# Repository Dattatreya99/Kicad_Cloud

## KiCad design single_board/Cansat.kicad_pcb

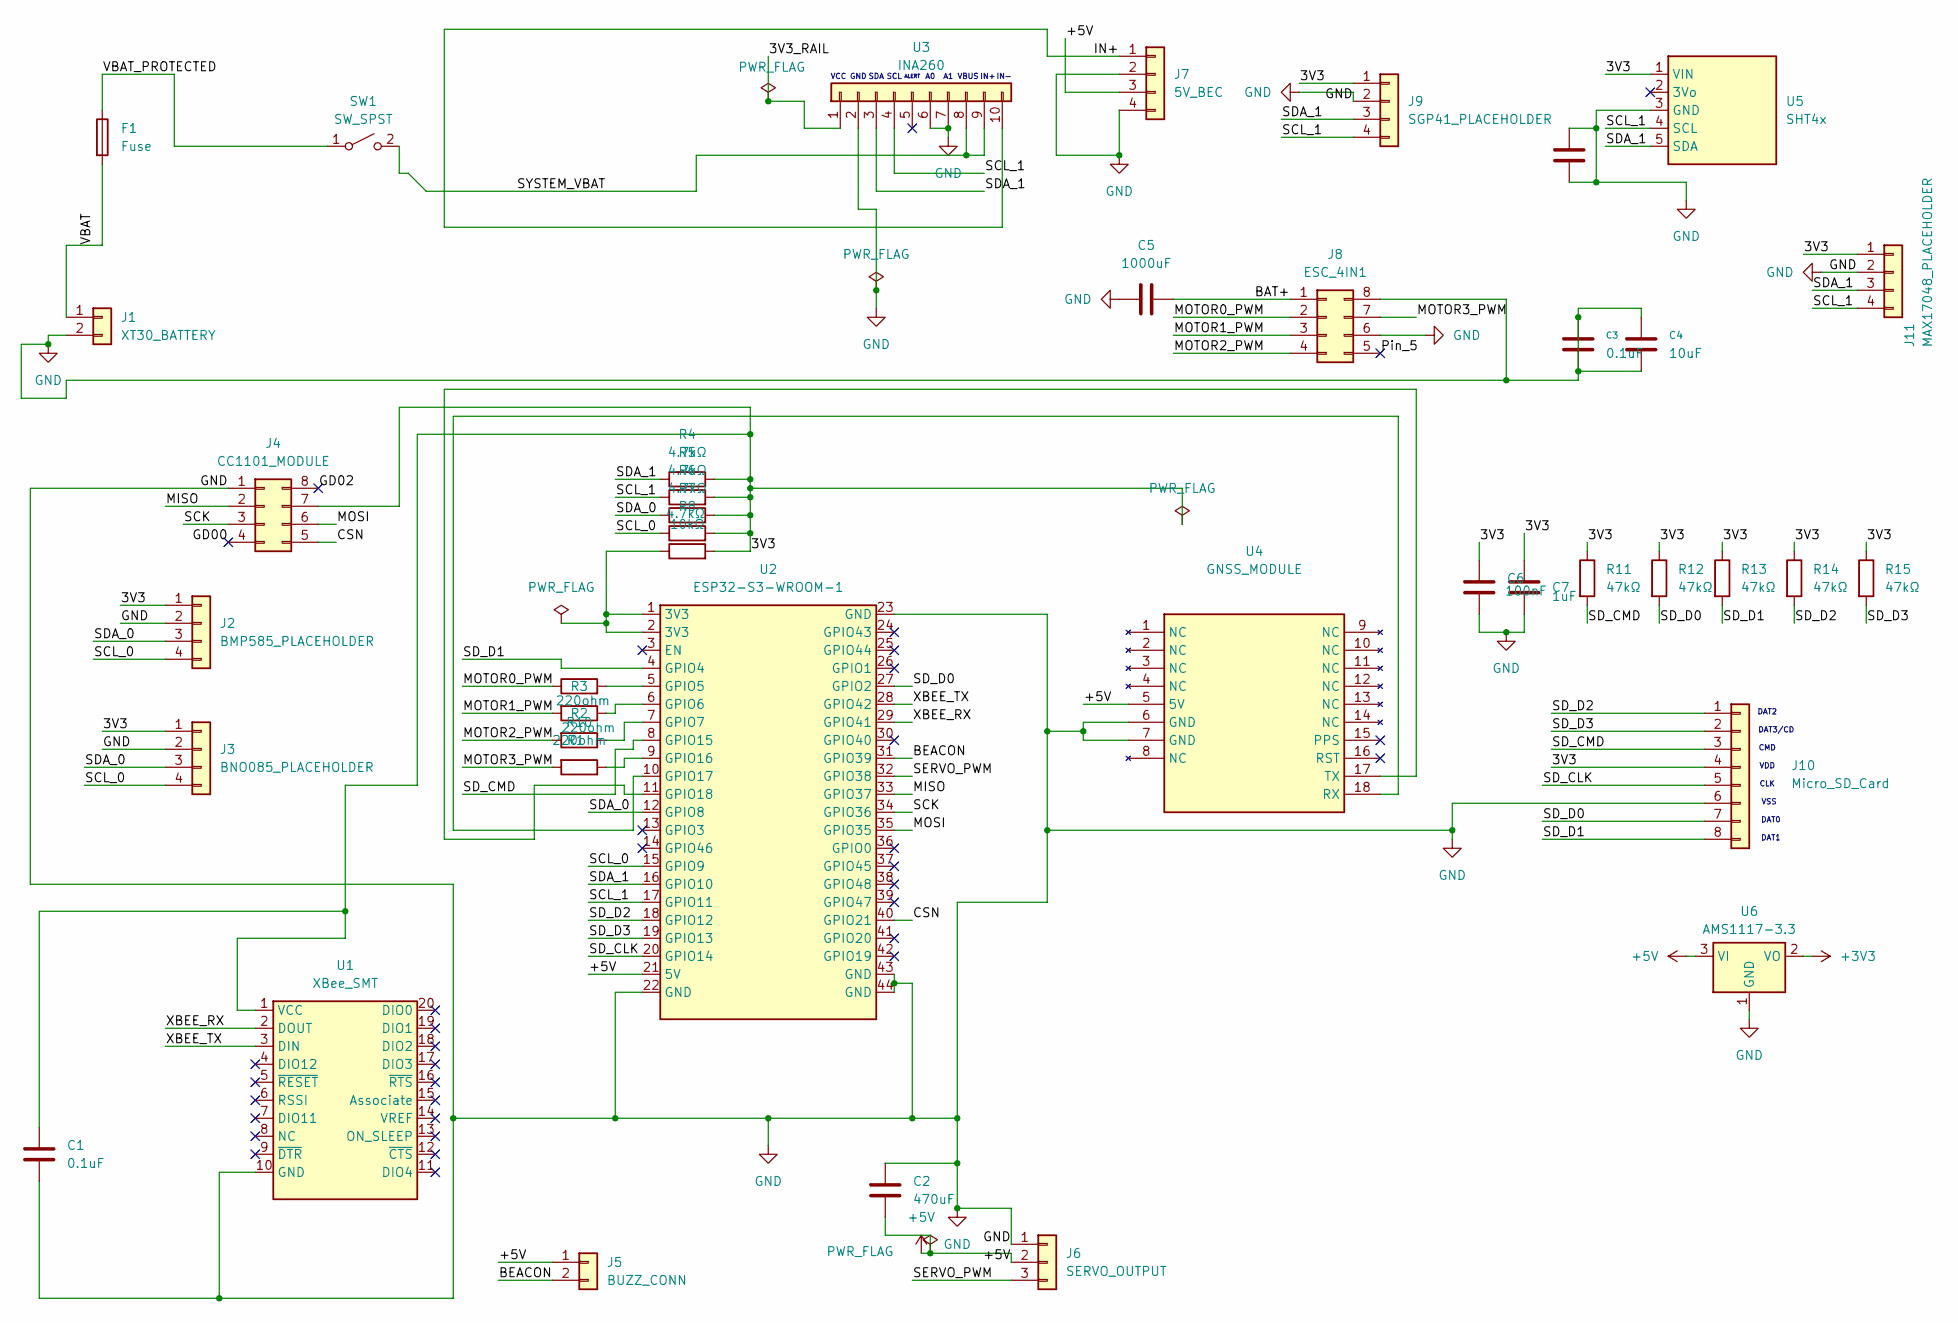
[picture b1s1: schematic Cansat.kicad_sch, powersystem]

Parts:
C1, C3: 0.1uF; C_Disc_D5.0mm_W2.5mm_P2.50mm
C2: 470uF; C_Disc_D5.0mm_W2.5mm_P2.50mm
C4: 10uF; CP_Radial_D5.0mm_P2.50mm
C5: 1000uF; CP_Radial_D10.0mm_P5.00mm
C6, C8: 100nF; C_Disc_D5.0mm_W2.5mm_P2.50mm
C7: 1uF; CP_Radial_D5.0mm_P2.50mm
F1: Fuse; Fuseholder_Cylinder-5x20mm_Bulgin_FX0456_Vertical_Closed
J1: XT30_BATTERY; AMASS_XT30UPB-M_1x02_P5.0mm_Vertical
J2: BMP585_PLACEHOLDER; BMP585_Breakout
J3: BNO085_PLACEHOLDER; BNO085_Breakout
J4: CC1101_MODULE; CC1101_Module
J5: BUZZ_CONN; PinSocket_1x02_P2.54mm_Vertical
J6: SERVO_OUTPUT; PinSocket_1x03_P2.54mm_Vertical
J7: 5V_BEC; 5V_BEC_Pololu
J8: ESC_4IN1; ESC_HAKRC_20A
J9: SGP41_PLACEHOLDER; SGP41_Breakout
J10: Micro_SD_Card; MicroSD_Breakout
J11: MAX17048_PLACEHOLDER; MAX17048_Breakout
R1, R2, R3, R10: 220ohm; R_Axial_DIN0207_L6.3mm_D2.5mm_P2.54mm_Vertical
R4, R5, R6, R7: 4.7kΩ; R_Axial_DIN0207_L6.3mm_D2.5mm_P2.54mm_Vertical
R8: 10kΩ; R_Axial_DIN0207_L6.3mm_D2.5mm_P2.54mm_Vertical
R11, R12, R13, R14, R15: 47kΩ; R_Axial_DIN0207_L6.3mm_D2.5mm_P2.54mm_Vertical
SW1: SW_SPST; SW_SPST_Omron_B3F-40xx
U1: XBee_SMT; XBee_3_Pro_TH
U2: ESP32-S3-WROOM-1; ESP32-S3-DevKitC
U3: INA260; INA260_Breakout
U4: GNSS_MODULE; Edgehax_NavIC
U5: SHT4x; PinSocket_1x05_P2.54mm_Vertical
U6: AMS1117-3.3; SOT-223-3_TabPin2

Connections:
+3V3: U6.2 (VO)
+5V: C2.2, J5.1, J6.2, J7.3, U2.21 (5V), U4.5 (5V), U6.3 (VI)
/3V3: C1.1, C6.1, C7.1, J2.1, J3.1, J4.7, J9.1, J10.4, J11.1, R4.2, R5.2, R6.2, R7.2, R8.2, R11.1, R12.1, R13.1, R14.1, R15.1, U1.1 (VCC), U5.1 (VIN)
/3V3_RAIL: U3.1
/BAT+: C5.2, J8.1
/BEACON: J5.2, U2.31 (GPIO39)
/CSN: J4.5, U2.40 (GPIO21)
/GD00: J4.4
/GD02: J4.8
/IN+: J7.1, U3.10
/MISO: J4.2, U2.33 (GPIO37)
/MOSI: J4.6, U2.35 (GPIO35)
/MOTOR0_PWM: J8.2, R3.1
/MOTOR1_PWM: J8.3, R2.2
/MOTOR2_PWM: J8.4, R1.2
/MOTOR3_PWM: J8.7, R10.2
/Pin_5: J8.5
/SCK: J4.3, U2.34 (GPIO36)
/SCL_0: J2.4, J3.4, R7.1, U2.15 (GPIO9)
/SCL_1: J9.4, J11.4, R5.1, U2.17 (GPIO11), U3.4, U5.4 (SCL)
/SDA_0: J2.3, J3.3, R6.1, U2.12 (GPIO8)
/SDA_1: J9.3, J11.3, R4.1, U2.16 (GPIO10), U3.3, U5.5 (SDA)
/SD_CLK: J10.5, U2.20 (GPIO14)
/SD_CMD: J10.3, R11.2, U2.8 (GPIO15)
/SD_D0: J10.7, R12.2, U2.27 (GPIO2)
/SD_D1: J10.8, R13.2, U2.4 (GPIO4)
/SD_D2: J10.1, R14.2, U2.18 (GPIO12)
/SD_D3: J10.2, R15.2, U2.19 (GPIO13)
/SERVO_PWM: J6.3, U2.32 (GPIO38)
/SYSTEM_VBAT: SW1.2 (B), U3.8, U3.9
/VBAT: F1.2, J1.1
/VBAT_PROTECTED: F1.1, SW1.1 (A)
/XBEE_RX: U1.2 (DOUT), U2.29 (GPIO41)
/XBEE_TX: U1.3 (DIN), U2.28 (GPIO42)
GND: C1.2, C2.1, C3.1, C3.2, C4.1, C4.2, C5.1, C6.2, C7.2, C8.1, C8.2, J1.2, J2.2, J3.2, J4.1, J6.1, J7.2, J7.4, J8.6, J8.8, J9.2, J10.6, J11.2, U1.10 (GND), U2.22 (GND), U2.23 (GND), U2.43 (GND), U2.44 (GND), U3.2, U3.6, U3.7, U4.6 (GND), U4.7 (GND), U5.3 (GND), U6.1 (GND)
unnamed: R8.1, U2.1 (3V3), U2.2 (3V3)
unnamed: R3.2, U2.5 (GPIO5)
unnamed: R2.1, U2.6 (GPIO6)
unnamed: R1.1, U2.7 (GPIO7)
unnamed: R10.1, U2.9 (GPIO16)
unnamed: U2.10 (GPIO17), U4.18 (RX)
unnamed: U2.11 (GPIO18), U4.17 (TX)

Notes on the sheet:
CMD
ALERT
DAT1
VCC
CLK
DAT0
SDA
DAT2
IN-
IN+
SCL
VBUS
GND
VSS
VDD
DAT3/CD

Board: 2 copper layers, 41 parts (0 on the bottom side), 37 nets, no tracks yet.

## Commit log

2026-06-07 Initial commit: KiCad project setup for Cansat
2026-06-07 Restore COLLABORATION.md guide for team workflow
2026-06-08 replaced GNSS with NavIC 1x06 header
2026-06-08 Fix V1: Implement proper symbols, SparkFun NEO-F10N, ESP32-S3 breakout, and resolve ERC errors
2026-06-09 Schematic Locked - Zero ERC Errors, Updated Breakouts
2026-06-09 PDR Bridge Architecture: Generated custom courtyards and board outlines
2026-06-09 3 PCB Design
2026-06-09 Add single_board variant (copy of project)
2026-06-09 Add single_board variant; copy library files; WIP before footprint fix
2026-06-10 before patcher
2026-06-10 Naming Warning removed
2026-06-10 Ready for PDR
